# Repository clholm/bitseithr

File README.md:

# bitseithr
DIY synth design that uses two AY-3-8912 chips

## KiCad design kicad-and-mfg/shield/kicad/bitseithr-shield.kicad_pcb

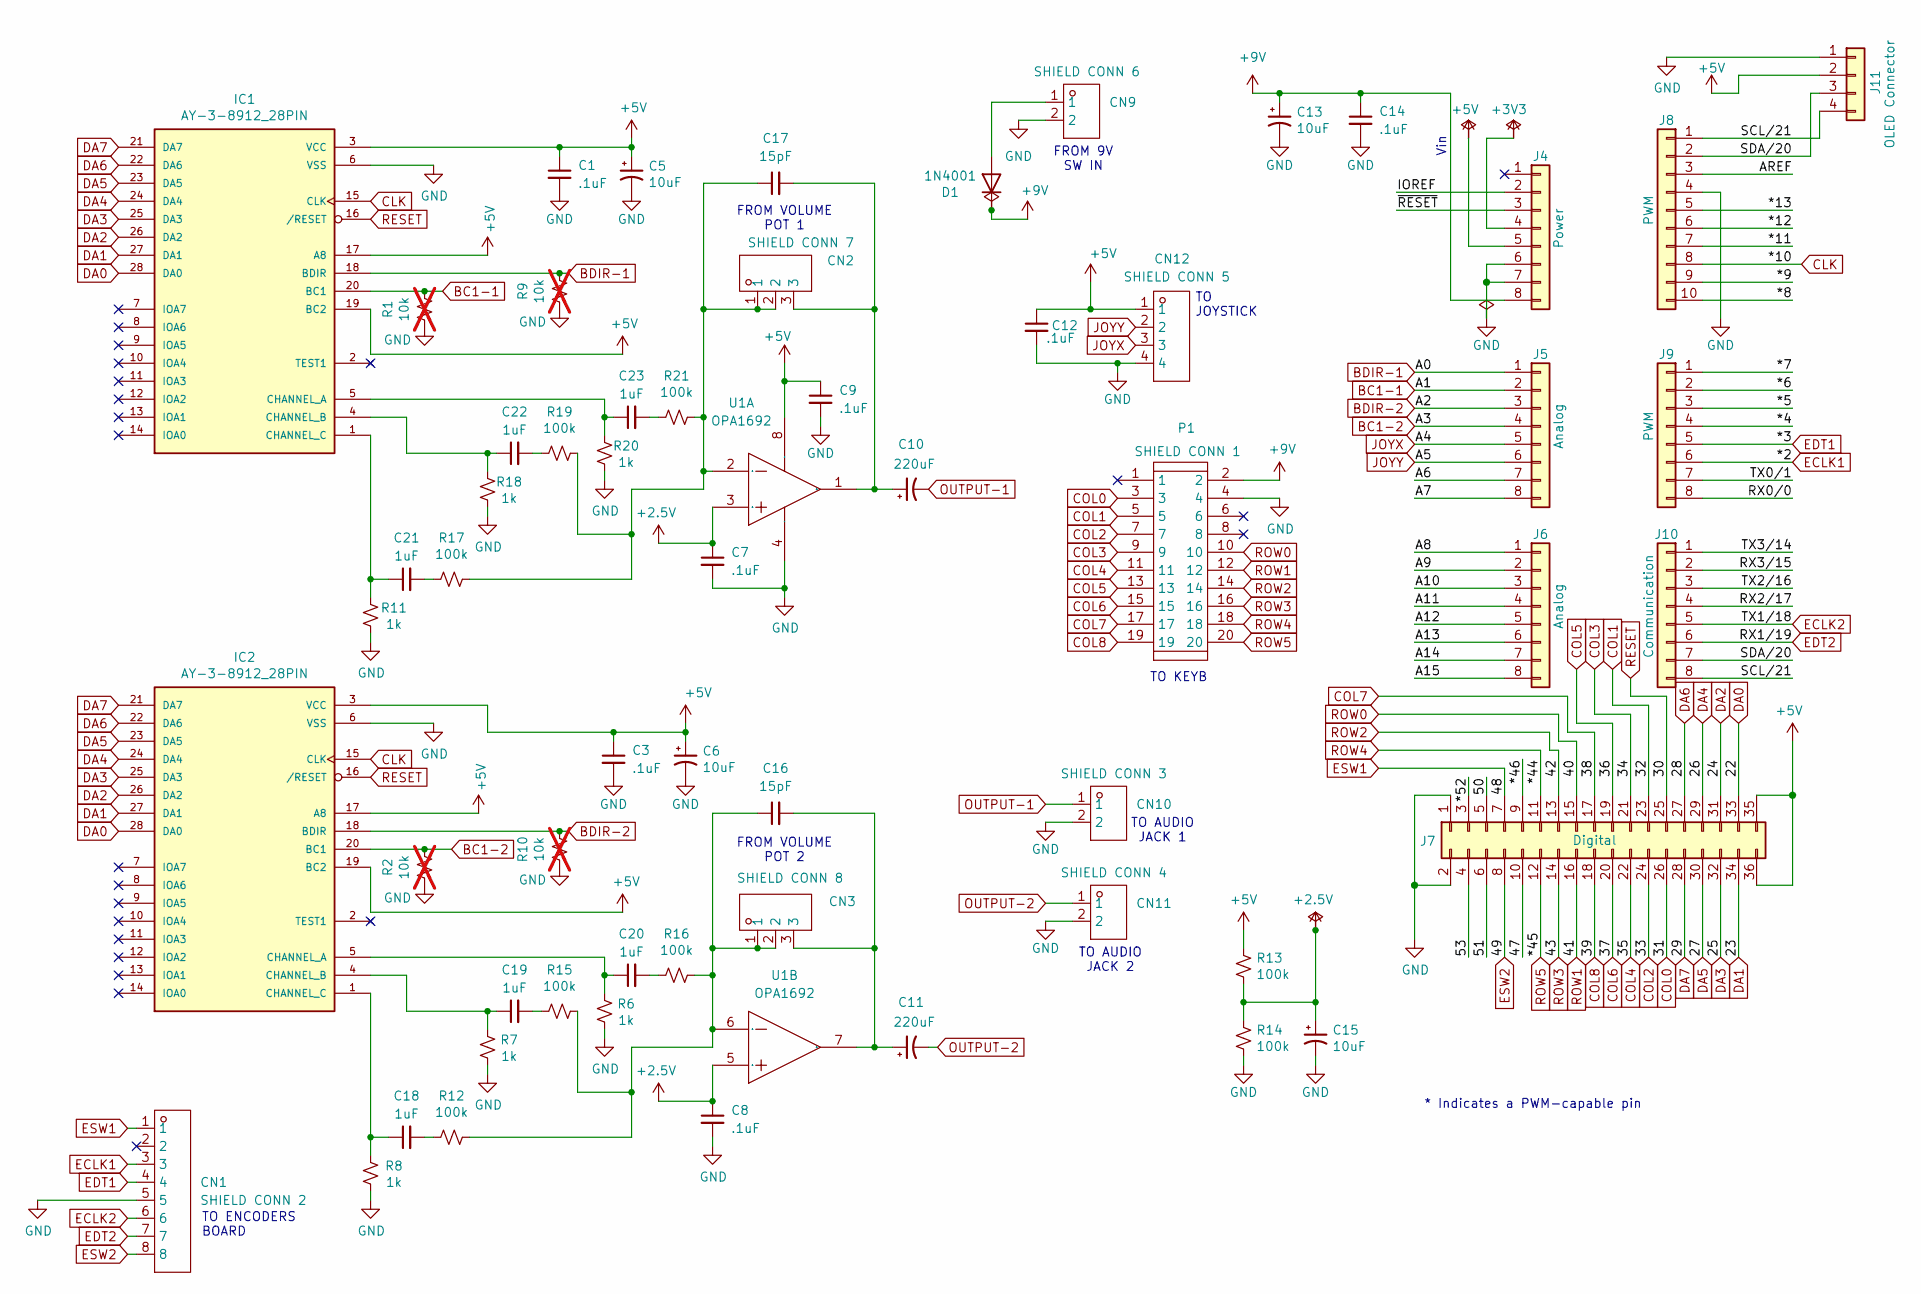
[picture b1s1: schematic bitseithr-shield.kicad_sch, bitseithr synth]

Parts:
C1, C3, C7, C8, C9, C12, C14: .1uF; C_0805_2012Metric; LCSC C49678
C5, C6, C13: 10uF; C_1206_3216Metric; LCSC C13585
C10, C11: 220uF; CP_Radial_D8.0mm_P3.50mm; LCSC C116228
C15: 10uF; CP_Radial_D5.0mm_P2.00mm; LCSC C88726
C16, C17: 15pF; C_0603_1608Metric; LCSC C1644
C18, C19, C20, C21, C22, C23: 1uF; C_Rect_L7.2mm_W5.0mm_P5.00mm; LCSC C92673
CN1: SHIELD CONN 2; CONN-TH_8P-P2.50_HCTL_HC-XA-8AW; LCSC C2845813
CN2: SHIELD CONN 7; CONN-TH_3P-P2.50_HCTL_HC-XA-3AW; LCSC C2845808
CN3: SHIELD CONN 8; CONN-TH_3P-P2.50_HCTL_HC-XA-3AW; LCSC C2845808
CN9: SHIELD CONN 6; CONN-TH_2P-P2.50_HCTL_HC-XA-2AW; LCSC C2845807
CN10: SHIELD CONN 3; CONN-TH_2P-P2.50_HCTL_HC-XA-2AW; LCSC C2845807
CN11: SHIELD CONN 4; CONN-TH_2P-P2.50_HCTL_HC-XA-2AW; LCSC C2845807
CN12: SHIELD CONN 5; CONN-TH_4P-P2.50_HCTL_HC-XA-4AW; LCSC C2845809
D1: 1N4001; D_SMA; LCSC C2909965
IC1, IC2: AY-3-8912_28PIN; DIP-28_W15.24mm_Socket
J4: Power; PinSocket_1x08_P2.54mm_Vertical
J5, J6: Analog; PinSocket_1x08_P2.54mm_Vertical
J7: Digital; PinSocket_2x18_P2.54mm_Vertical
J8: PWM; PinSocket_1x10_P2.54mm_Vertical
J9: PWM; PinSocket_1x08_P2.54mm_Vertical
J10: Communication; PinSocket_1x08_P2.54mm_Vertical
J11: OLED Connector; JST_SH_SM04B-SRSS-TB_1x04-1MP_P1.00mm_Horizontal; LCSC C160404
P1: SHIELD CONN 1; IDC-TH_20P-L33.0-W13.8-H-M-R2-C10-P2.54-S2.54-TR; LCSC C9144
R1, R2, R9, R10: 10k; R_Axial_DIN0207_L6.3mm_D2.5mm_P7.62mm_Horizontal; not fitted
R6, R7, R8, R11, R18, R20: 1k; R_0603_1608Metric; LCSC C110776
R12, R13, R14, R15, R16, R17, R19, R21: 100k; R_1206_3216Metric; LCSC C2073484
U1: OPA1692; SOIC-8_L4.9-W3.9-P1.27-LS6.0-BL; LCSC C2060550

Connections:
+2.5V: C7.1, C8.1, C15.1, R13.2, R14.1, U1.3 (IN1+), U1.5 (IN2+)
+3V3: J4.4
+5V: C1.1, C3.1, C5.1, C6.1, C9.1, C12.1, CN12.1, IC1.3 (VCC), IC1.17 (A8), IC1.19 (BC2), IC2.3 (VCC), IC2.17 (A8), IC2.19 (BC2), J4.5, J7.35, J7.36, J11.2, R13.1, U1.8 (V+)
+9V: C13.1, C14.1, D1.1 (K), J4.8, P1.2
/47: J7.10
/50: J7.5
/51: J7.6
/53: J7.4
/*4: J9.4
/*5: J9.3
/*6: J9.2
/*7: J9.1
/*8: J8.10
/*9: J8.9
/*11: J8.7
/*12: J8.6
/*13: J8.5
/*46: J7.9
/*52: J7.3
/A6: J5.7
/A7: J5.8
/A8: J6.1
/A9: J6.2
/A10: J6.3
/A11: J6.4
/A12: J6.5
/A13: J6.6
/A14: J6.7
/A15: J6.8
/AREF: J8.3
/IOREF: J4.2
/RX0/0: J9.8
/RX2/17: J10.4
/RX3/15: J10.2
/SCL/21: J8.1, J10.8, J11.4
/SDA/20: J8.2, J10.7, J11.3
/TX0/1: J9.7
/TX2/16: J10.3
/TX3/14: J10.1
/~RESET: J4.3
BC1-1: IC1.20 (BC1), J5.2, R1.1
BC1-2: IC2.20 (BC1), J5.4, R2.1
BDIR-1: IC1.18 (BDIR), J5.1, R9.1
BDIR-2: IC2.18 (BDIR), J5.3, R10.1
CLK: IC1.15 (CLK), IC2.15 (CLK), J8.8
COL0: J7.26, P1.3
COL1: J7.23, P1.5
COL2: J7.24, P1.7
COL3: J7.21, P1.9
COL4: J7.22, P1.11
COL5: J7.19, P1.13
COL6: J7.20, P1.15
COL7: J7.17, P1.17
COL8: J7.18, P1.19
DA0: IC1.28 (DA0), IC2.28 (DA0), J7.33
DA1: IC1.27 (DA1), IC2.27 (DA1), J7.34
DA2: IC1.26 (DA2), IC2.26 (DA2), J7.31
DA3: IC1.25 (DA3), IC2.25 (DA3), J7.32
DA4: IC1.24 (DA4), IC2.24 (DA4), J7.29
DA5: IC1.23 (DA5), IC2.23 (DA5), J7.30
DA6: IC1.22 (DA6), IC2.22 (DA6), J7.27
DA7: IC1.21 (DA7), IC2.21 (DA7), J7.28
ECLK1: CN1.3, J9.6
ECLK2: CN1.6, J10.5
EDT1: CN1.4, J9.5
EDT2: CN1.7, J10.6
ESW1: CN1.1, J7.7
ESW2: CN1.8, J7.8
GND: C1.2, C3.2, C5.2, C6.2, C7.2, C8.2, C9.2, C12.2, C13.2, C14.2, C15.2, CN1.5, CN9.2, CN10.2, CN11.2, CN12.4, IC1.6 (VSS), IC2.6 (VSS), J4.6, J4.7, J7.1, J7.2, J8.4, J11.1, P1.4, R1.2, R2.2, R6.1, R7.1, R8.1, R9.2, R10.2, R11.1, R14.2, R18.1, R20.1, U1.4 (V-)
JOYX: CN12.3, J5.5
JOYY: CN12.2, J5.6
unnamed: C18.2, R12.2
unnamed: C19.2, R15.2
unnamed: C20.2, R16.2
unnamed: C21.2, R17.2
unnamed: C22.2, R19.2
unnamed: C23.2, R21.2
unnamed: CN9.1, D1.2 (A)
unnamed: C23.1, IC1.5 (CHANNEL_A), R20.2
unnamed: C22.1, IC1.4 (CHANNEL_B), R18.2
unnamed: C21.1, IC1.1 (CHANNEL_C), R11.2
unnamed: C20.1, IC2.5 (CHANNEL_A), R6.2
unnamed: C19.1, IC2.4 (CHANNEL_B), R7.2
unnamed: C18.1, IC2.1 (CHANNEL_C), R8.2
unnamed: C17.1, CN2.1, CN2.2, R17.1, R19.1, R21.1, U1.2 (IN1-)
unnamed: C10.1, C17.2, CN2.3, U1.1 (OUT1)
unnamed: C16.1, CN3.1, CN3.2, R12.1, R15.1, R16.1, U1.6 (IN2-)
unnamed: C11.1, C16.2, CN3.3, U1.7 (OUT2)
OUTPUT-1: C10.2, CN10.1
OUTPUT-2: C11.2, CN11.1
RESET: IC1.16 (/RESET), IC2.16 (/RESET), J7.25
ROW0: J7.15, P1.10
ROW1: J7.16, P1.12
ROW2: J7.13, P1.14
ROW3: J7.14, P1.16
ROW4: J7.11, P1.18
ROW5: J7.12, P1.20

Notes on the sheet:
TO AUDIO JACK 2
FROM VOLUME POT 1
TO AUDIO JACK 1
Vin
TO JOYSTICK
FROM 9V SW IN
FROM VOLUME POT 2
* Indicates a PWM-capable pin
TO KEYB
TO ENCODERS BOARD

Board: 2 copper layers, 65 parts (0 on the bottom side), 62 nets, no tracks yet.

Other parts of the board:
MH1, MH2, MH3, MH4, MH5, MH6: MountingHole_3.2mm

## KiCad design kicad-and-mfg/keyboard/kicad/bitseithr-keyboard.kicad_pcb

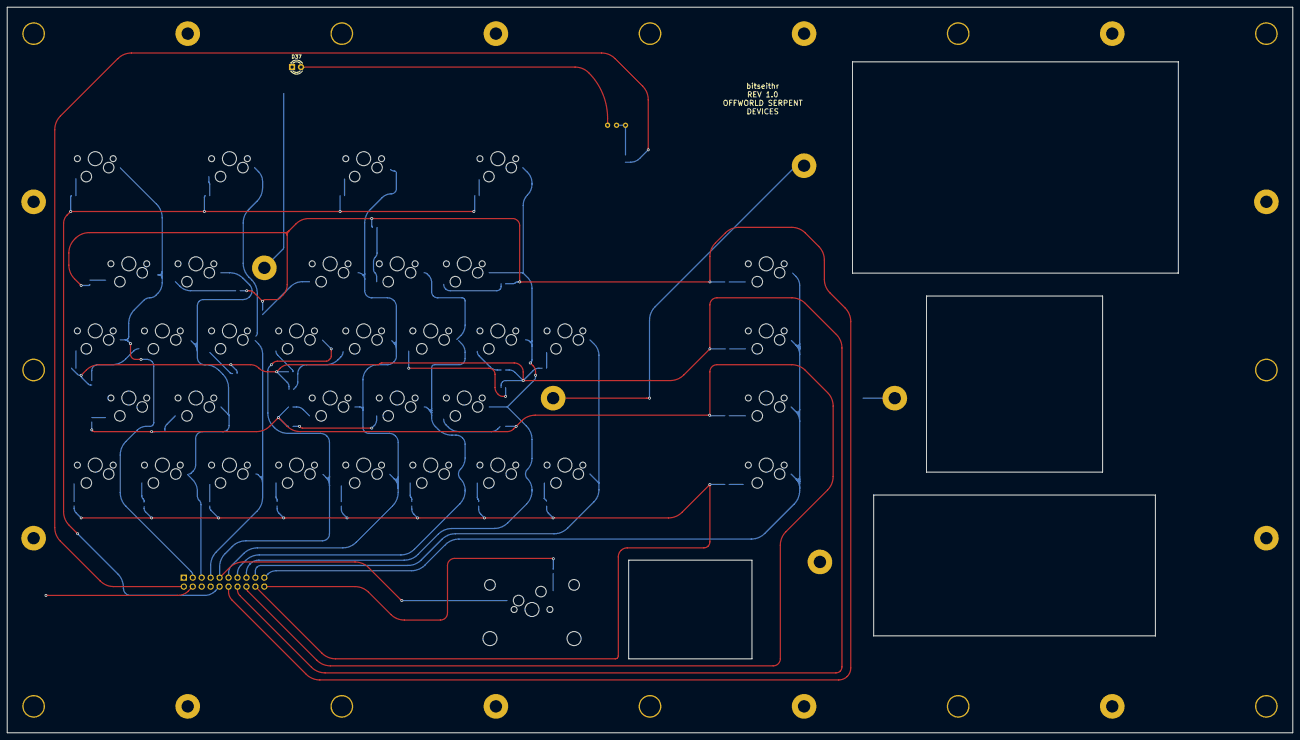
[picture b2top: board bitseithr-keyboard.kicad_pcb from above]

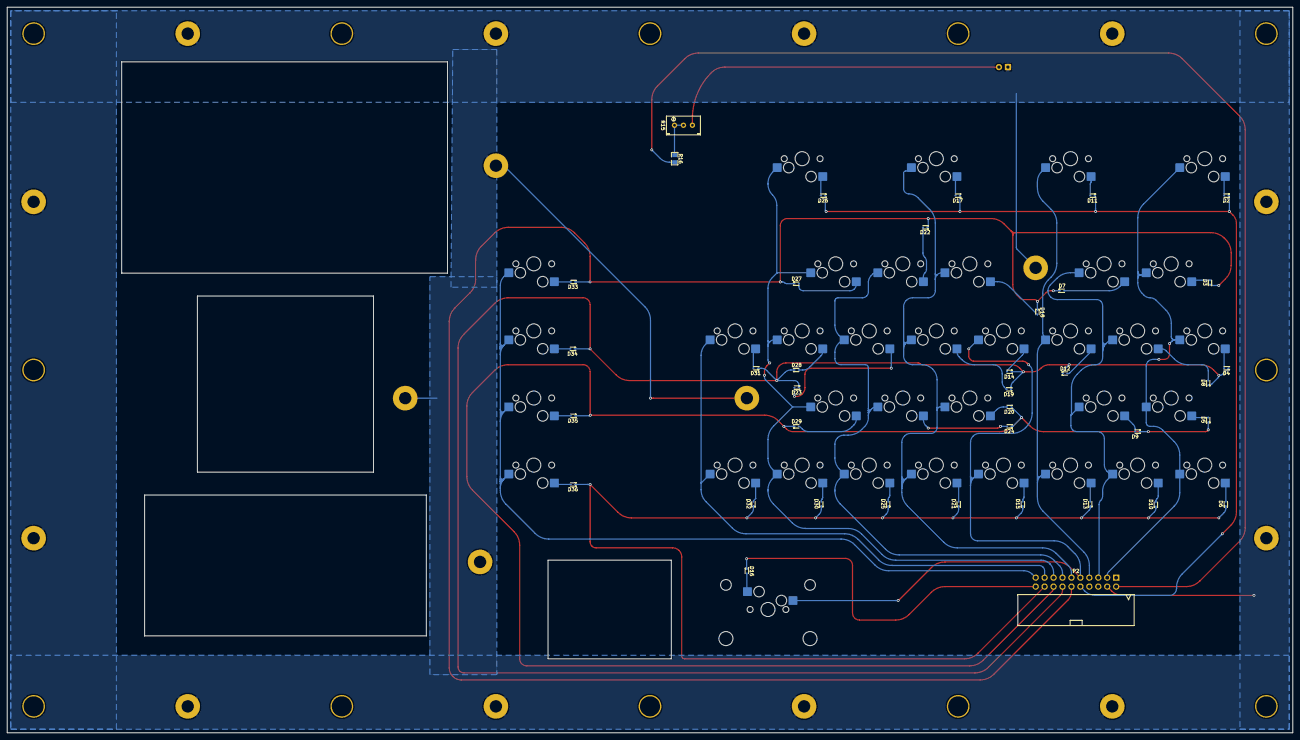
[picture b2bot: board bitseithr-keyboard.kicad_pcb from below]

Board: 2 copper layers, 365.0 x 206.0 mm, 103 parts (73 on the bottom side), 54 nets.

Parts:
D2, D3, D4, D5, D6, D7, D8, D9, D10, D11, D12, D13, D14, D15, D16, D17, D18, D19, D20, D21, D22, D23, D24, D25, D26, D27, D28, D29, D30, D31, D32, D33, D34, D35, D36: 1N4148; SOD-523_L1.2-W0.8-LS1.6-RD-1
D37: POWER LED; LED_D3.0mm
HOLE: M3-hole; MountingHole_M3_GND_7mm
HOLE#2, HOLE#3, HOLE#4, HOLE#5, HOLE#6, HOLE#7, HOLE#8, HOLE#9, HOLE#10, HOLE#11, HOLE#12, HOLE#13, HOLE#14, HOLE#15, HOLE#16, HOLE#29: M3-hole; MountingHole_M3_GND_7mm
HOLE#17, HOLE#18, HOLE#19, HOLE#20, HOLE#21, HOLE#22, HOLE#23, HOLE#24, HOLE#25, HOLE#26, HOLE#27, HOLE#28: 5.7mm-hole; MountingHole_5.7mm
MX1, MX2, MX3, MX4, MX5, MX6, MX7, MX8, MX9, MX10, MX11, MX12, MX13, MX14, MX16, MX17, MX18, MX19, MX20, MX21, MX22, MX23, MX24, MX25, MX26, MX27, MX28, MX29, MX30, MX31, MX32, MX33, MX34, MX35: MX-NoLED; MX-Hotswap-1U
MX15: MX-NoLED; MX-Hotswap-2.25U
P2: KEYB CONN 1; IDC-TH_20P-L33.0-W13.8-H-M-R2-C10-P2.54-S2.54-TR
R15: 1kΩ; RES-ADJ-TH_3296W
R16: 330R; R0805

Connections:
+9V: P2.2, R16.2
COL0: MX1.1 (COL), MX2.1 (COL), MX3.1 (COL), MX4.1 (COL), MX5.1 (COL), P2.3
COL1: MX6.1 (COL), MX7.1 (COL), MX8.1 (COL), MX9.1 (COL), P2.5
COL2: MX10.1 (COL), MX11.1 (COL), MX12.1 (COL), P2.7
COL3: MX13.1 (COL), MX14.1 (COL), MX15.1 (COL), P2.9
COL4: MX16.1 (COL), MX17.1 (COL), MX18.1 (COL), MX19.1 (COL), MX20.1 (COL), P2.11
COL5: MX21.1 (COL), MX22.1 (COL), MX23.1 (COL), MX24.1 (COL), P2.13
COL6: MX25.1 (COL), MX26.1 (COL), MX27.1 (COL), MX28.1 (COL), MX29.1 (COL), P2.15
COL7: MX30.1 (COL), MX31.1 (COL), P2.17
COL8: MX32.1 (COL), MX33.1 (COL), MX34.1 (COL), MX35.1 (COL), P2.19
GND: D37.1 (K), HOLE.1, HOLE#2.1, HOLE#3.1, HOLE#4.1, HOLE#5.1, HOLE#6.1, HOLE#7.1, HOLE#8.1, HOLE#9.1, HOLE#10.1, HOLE#11.1, HOLE#12.1, HOLE#13.1, HOLE#14.1, HOLE#15.1, HOLE#16.1, HOLE#29.1, P2.4
unnamed: D2.2 (A), MX1.2 (ROW)
unnamed: D3.2 (A), MX2.2 (ROW)
unnamed: D4.2 (A), MX3.2 (ROW)
unnamed: D5.2 (A), MX4.2 (ROW)
unnamed: D6.2 (A), MX5.2 (ROW)
unnamed: D7.2 (A), MX6.2 (ROW)
unnamed: D8.2 (A), MX7.2 (ROW)
unnamed: D9.2 (A), MX8.2 (ROW)
unnamed: D10.2 (A), MX9.2 (ROW)
unnamed: D11.2 (A), MX10.2 (ROW)
unnamed: D12.2 (A), MX11.2 (ROW)
unnamed: D13.2 (A), MX12.2 (ROW)
unnamed: D14.2 (A), MX13.2 (ROW)
unnamed: D15.2 (A), MX14.2 (ROW)
unnamed: D16.2 (A), MX15.2 (ROW)
unnamed: D17.2 (A), MX16.2 (ROW)
unnamed: D18.2 (A), MX17.2 (ROW)
unnamed: D19.2 (A), MX18.2 (ROW)
unnamed: D20.2 (A), MX19.2 (ROW)
unnamed: D21.2 (A), MX20.2 (ROW)
unnamed: D22.2 (A), MX21.2 (ROW)
unnamed: D23.2 (A), MX22.2 (ROW)
unnamed: D24.2 (A), MX23.2 (ROW)
unnamed: D25.2 (A), MX24.2 (ROW)
unnamed: D26.2 (A), MX25.2 (ROW)
unnamed: D27.2 (A), MX26.2 (ROW)
unnamed: D28.2 (A), MX27.2 (ROW)
unnamed: D29.2 (A), MX28.2 (ROW)
unnamed: D30.2 (A), MX29.2 (ROW)
unnamed: D31.2 (A), MX30.2 (ROW)
unnamed: D32.2 (A), MX31.2 (ROW)
unnamed: D33.2 (A), MX32.2 (ROW)
unnamed: D34.2 (A), MX33.2 (ROW)
unnamed: D35.2 (A), MX34.2 (ROW)
unnamed: D36.2 (A), MX35.2 (ROW)
unnamed: D37.2 (A), R15.3
unnamed: R15.1, R15.2, R16.1
ROW0: D2.1 (K), D11.1 (K), D17.1 (K), D26.1 (K), P2.10
ROW1: D3.1 (K), D7.1 (K), D18.1 (K), D22.1 (K), D27.1 (K), D33.1 (K), P2.12
ROW2: D4.1 (K), D8.1 (K), D12.1 (K), D14.1 (K), D19.1 (K), D23.1 (K), D28.1 (K), D31.1 (K), D34.1 (K), P2.14
ROW3: D5.1 (K), D9.1 (K), D20.1 (K), D24.1 (K), D29.1 (K), D35.1 (K), P2.16
ROW4: D6.1 (K), D10.1 (K), D13.1 (K), D15.1 (K), D21.1 (K), D25.1 (K), D30.1 (K), D32.1 (K), D36.1 (K), P2.18
ROW5: D16.1 (K), P2.20

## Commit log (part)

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2026-02-20 initial schematic commit
2026-02-21 schematic progress
2026-02-21 almost done with complete schematic
2026-02-21 more schematic updates
2026-02-21 still workin. i'm crazy
2026-02-21 schematic continued
2026-02-21 saving op-amp config before I mess with the feedback resistor
2026-02-21 i think the schematic is done
2026-02-22 erc and llm review complete
2026-02-22 minor revisions to the op-amp sections
2026-02-22 re-annotate
2026-02-22 idk why i had to save again but this should be it for v1 of the schematic
2026-02-28 splitting out schematic to begin designing the boards
2026-04-20 continued work on keyboard pcb
2026-04-24 continued keyboard pcb
2026-04-25 updated control scheme layout
2026-04-25 arranged diodes on board
2026-04-25 shrank board length
2026-05-23 moved some diodes around
2026-06-13 updated keyboard connector pinout for better trace routing (hopefully)
2026-06-14 fixed unclosed inner cutout, began key matrix traces
2026-06-14 updated keyboard connector pinout again for better routing
2026-06-14 keyboard pcb ~mostly done (still need to ground the mounting holes)
2026-06-15 removed inner layers, added ground plane on bottom
2026-06-15 some routing updates
2026-06-15 drc fixes
2026-06-16 wavy traces :wave:
2026-06-16 fixed drc warning
2026-06-19 changeed path, migrated to kicad 10
2026-06-19 fixed drc from kicad 10 upgrade, but origin has shifted 1.5 mm left (means board coords are +1.5mm)
2026-06-19 moved keyboard pcb 1.5mm left, started shield schematic
2026-06-19 made one tiny re-route, fixed drc warnings from that
2026-06-21 shield schematic cleanup. fixed sound output section (using op amps as inverting summer now too)
2026-06-22 fixed some naming issues
2026-06-23 removed unneeded components from the shield schematic
